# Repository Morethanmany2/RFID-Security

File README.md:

# RFID-Security

Designed a circuit that allows an user only with an authorised NFC tag.

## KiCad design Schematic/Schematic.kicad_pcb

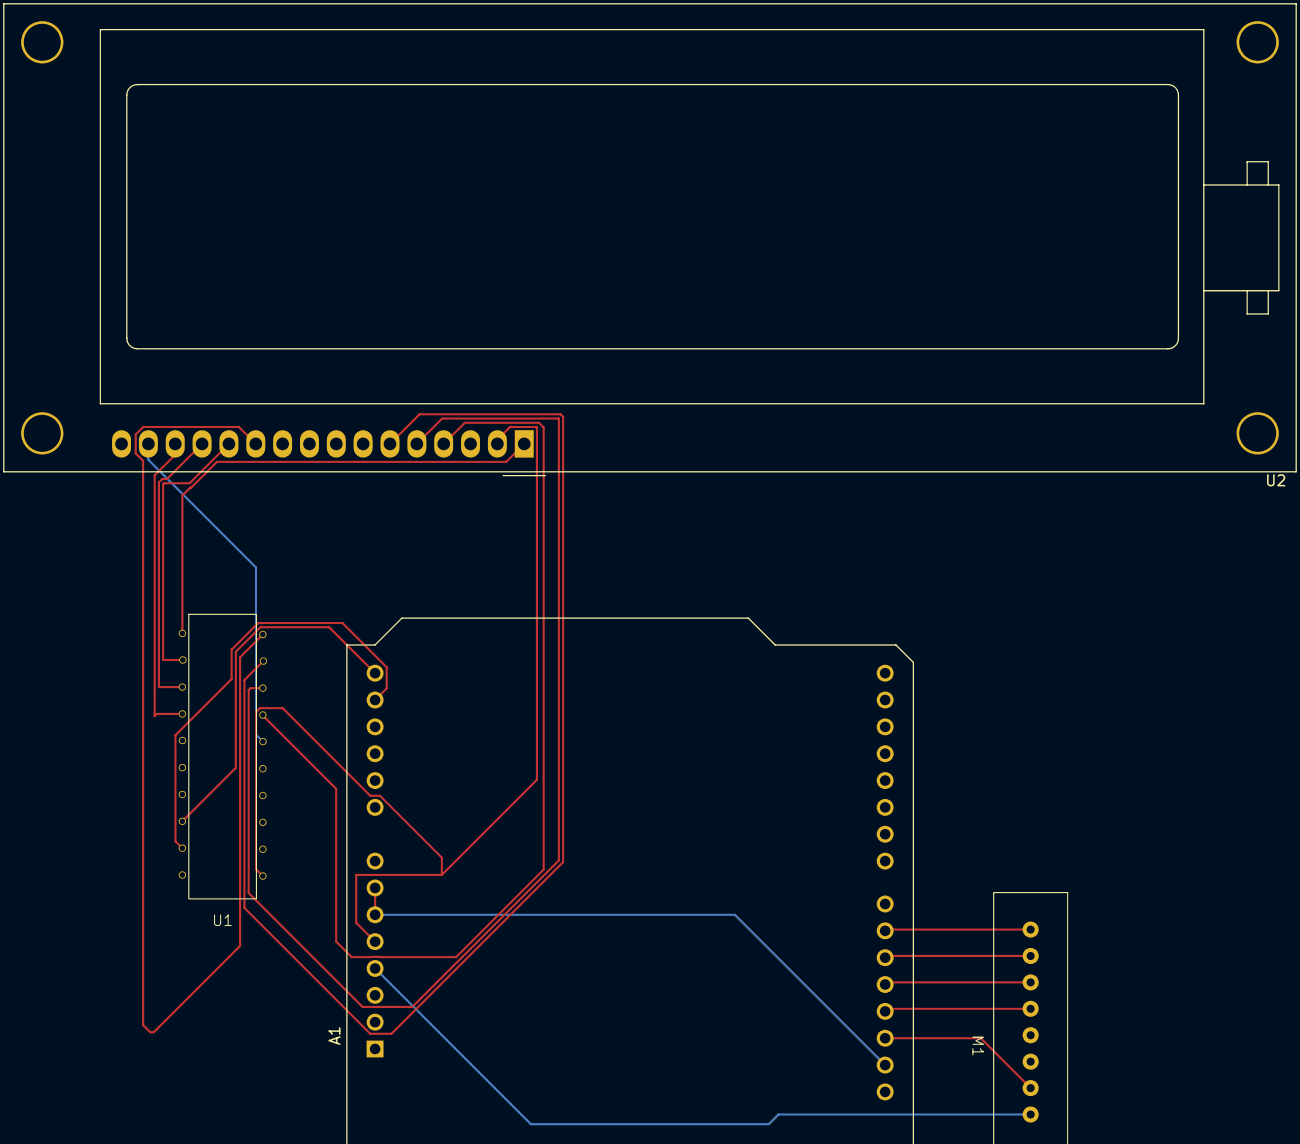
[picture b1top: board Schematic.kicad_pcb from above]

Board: 2 copper layers, 4 parts (0 on the bottom side), 19 nets.

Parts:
A1: Arduino_UNO_R2
M1: RFID-RC522; RFID-reader module
U1: PCF8584; PCF8584-1
U2: LCD-16X2; HY1602E

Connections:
/3V3: A1.4 (3V3), M1.8 (3V3)
/+5V: A1.5 (+5V), U1.20 (VDD), U2.2 (VDD)
/A: U1.15 (D7), U2.15 (A)
/DB4: U1.11 (D3), U2.11 (DB4)
/DB5: U1.9 (D2), U2.12 (DB5)
/DB6: U1.8 (D1), U2.13 (DB6)
/DB7: U1.7 (D0), U2.14 (DB7)
/E: U1.12 (D4), U2.6 (E)
/MISO: A1.27 (D12), M1.4 (MISO)
/MOSI: A1.26 (D11), M1.3 (MOSI)
/RS: U1.14 (D6), U2.4 (RS)
/RST: A1.28 (D13), M1.7 (RST)
/R/W: U1.13 (D5), U2.5 (R/W)
/SCK: A1.25 (D10), M1.2 (SCK)
/SCL/A5: A1.14 (SCL/A5), U1.3 (SCL)
/SDA: A1.24 (D9), M1.1 (SDA)
/SDA/A4: A1.13 (SDA/A4), U1.2 (SDA)
unnamed: A1.6 (GND), A1.7 (GND), A1.29 (GND)
unnamed: U1.10 (VSS), U2.1 (VSS)
